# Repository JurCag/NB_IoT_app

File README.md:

# NB-IoT Application

Table of contents:
- [Introduction](#introduction)
- [System Architecture](#system-architecture)
- [Web Application](#web-application)
- [Firmware and Hardware](#firmware-and-hardware)
    - [Communication overview](#communication-overview)
    - [Development tools](#development-tools)
  - [NB-IoT Concentrator](#nb-iot-concentrator)
    - [Firmware](#firmware)
    - [Hardware](#hardware)
  - [Sensor Boards](#sensor-boards)
    - [Firmware](#firmware)
    - [Hardware](#hardware)
 
#### Introduction:
Project showcases the application of NB-IoT technology for uploading data to the cloud. 
Hardware involves an NB-IoT concentrator and 6 sensor nodes equipped with different sensors, specifically designed to measure parameters of a [photobioreactor](https://en.wikipedia.org/wiki/Photobioreactor).<br />
Simple concept of the application including PBR is available [here](https://github.com/JurCag/NB_IoT_app/blob/master/images/photobioreactor.svg).

#### System Architecture:
<div align="center">

</div>

## Web Application

#### Description:
Simple web application for sensor data visualization and control of NB-IoT concentrator.

#### External libraries:
- AWS SDK: to access AWS services
- JSZip: to manipulate ZIP files
- Highcharts: data visualization

## Firmware and Hardware

#### Communication overview:
The application uses [MQTT](https://mqtt.org/) protocol to communicate with broker within the AWS IoT Core. MQTT topics and structure of JSON payloads sent in the messages is shown below.
1) The concentrator provisions new nodes into the BLE mesh network. Nodes provide their descriptors.
2) The user requests the node measurement period by publishing a message to the topic: **BG96_demoThing/mmtPeriods/command**.
3) The concentrator responds with the current measurement period of that node to the topic: **BG96_demoThing/mmtPeriods/response**.
4) The user can change the node measurement period (e.g. 10 minutes).
5) The concentrator confirms the change by repeating the message.
6) The concentrator stores the measurement period value into the NVS (Non-Volatile Storage) memory.
7) When the counter reaches the specified period, the concentrator requests data from the sensor node over the BLE mesh.
8) The sensor node sends measured data.
9) The concentrator uploads the sensory data to AWS on the MQTT topic: **BG96_demoThing/sensors/\<nodeName\>**.
  
<div align="center">
  
</div>

#### Development tools:
- VSCode + [PlatformIO](https://platformio.org/)
- Framework: ESP-IDF (within platformio project, no need to install separately)

### NB-IoT Concentrator 
#### Firmware:
- The concentrator, acting as a master device, collects measurement data from sensor nodes and uploads it to the AWS IoT Core.
- The concentrator also establishes a local BLE mesh network and provisions other nodes into the network.
- BLE mesh models implemented by concentrator:
  - Configuration Server
  - Configuration Client
  - Sensor Client 

#### Hardware:
[Custom PCB board](https://github.com/JurCag/NB_IoT_app/tree/master/NB-IoT_PCB_rev_1_1) with ESP32-C3 controller and Quectel BG96 module.

| Component     | Link  |
| :-----------  |:---------------:|
| **MCU**                 | [ESP32-C3](https://www.espressif.com/en/products/socs/esp32-c3) |
| **NB-IoT module**       | [Quectel BG96](https://www.quectel.com/product/lpwa-bg96-cat-m1-nb1-egprs) |
| **NB-IoT module board** | [LTE IoT 2 Click](https://www.mikroe.com/lte-iot-2-click) |
| **NB-IoT concentrator** | [NB-IoT_PCB_rev_1_1](https://github.com/JurCag/NB_IoT_app/tree/master/NB-IoT_PCB_rev_1_1) |

### Sensor boards
#### Firmware:
- Each sensor node incorporates the same BLE mesh models.
- BLE mesh models implemented by sensor nodes:
  - Configuration Server
  - Sensor Server 
  - Sensor Setup Server 
- The drivers are specific to the corresponding sensor they are equipped with.

#### Hardware:
 - **Control board:<br />**
 Each sensor node has the same control board: [ESP32-C3-DevKitC-02](https://docs.espressif.com/projects/esp-idf/en/latest/esp32c3/hw-reference/esp32c3/user-guide-devkitc-02.html)

 - **Sensors:<br />**

| Physical quantities        |     Sensor        |  Connection     | 
| :-----------: |:---------------:|:---------------:|
| temperature,<br /> humidity,<br /> pressure | BME280    ||
| pH                                          | PH4502C   ||
| CO_2 concentration                          | MHZ19B    ||
| light intensity                             | GL5528    ||
| turbidity                                   | TS300B    ||
| electric current                            | ACS712    ||

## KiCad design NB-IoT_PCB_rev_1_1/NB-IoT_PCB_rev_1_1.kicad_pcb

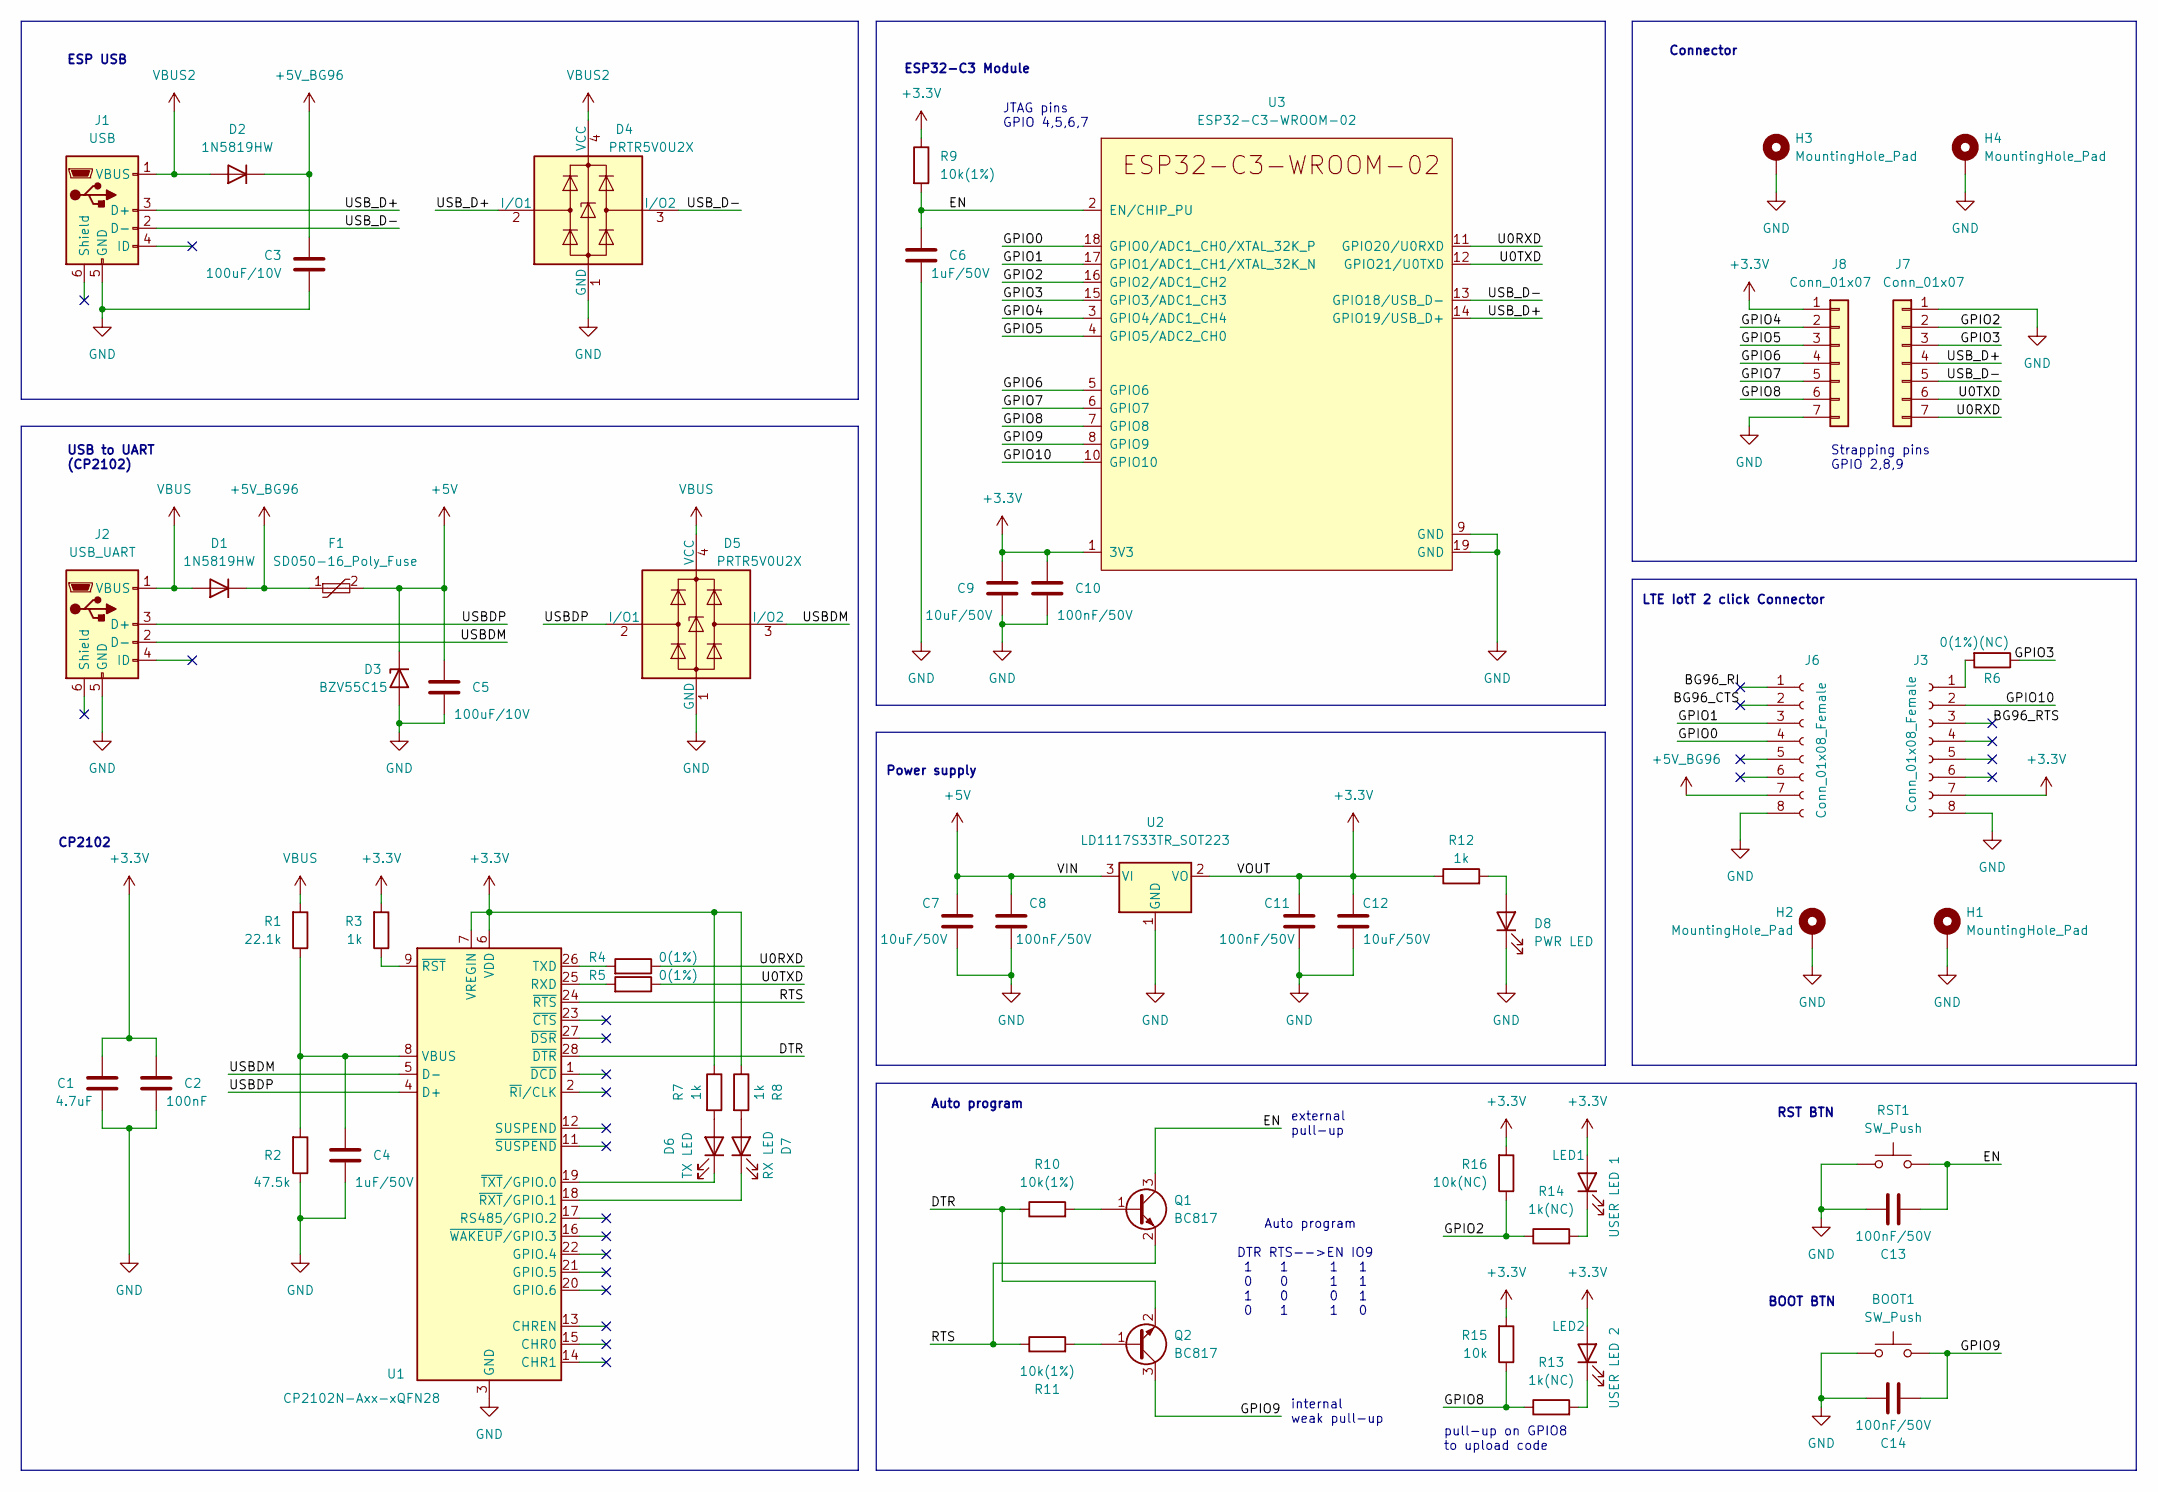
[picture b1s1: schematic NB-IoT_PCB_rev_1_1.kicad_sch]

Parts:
BOOT1: SW_Push; SW_PUSH_6mm_H5mm
C1: 4.7uF; C_1210_3225Metric_Pad1.33x2.70mm_HandSolder
C2: 100nF; C_0603_1608Metric_Pad1.08x0.95mm_HandSolder
C3, C5: 100uF/10V; CP_Radial_D5.0mm_P2.00mm
C4, C6: 1uF/50V; C_0603_1608Metric_Pad1.08x0.95mm_HandSolder
C7, C12: 10uF/50V; C_0805_2012Metric_Pad1.18x1.45mm_HandSolder
C8, C10, C11, C13, C14: 100nF/50V; C_0603_1608Metric_Pad1.08x0.95mm_HandSolder
C9: 10uF/50V; C_1206_3216Metric_Pad1.33x1.80mm_HandSolder
D1, D2: 1N5819HW; SOD3715X145N
D3: BZV55C15; D_MiniMELF
D4, D5: PRTR5V0U2X; SOT-143_Handsoldering
D6: TX LED; D_0805_2012Metric_Pad1.15x1.40mm_HandSolder
D7: RX LED; D_0805_2012Metric_Pad1.15x1.40mm_HandSolder
D8: PWR LED; D_0805_2012Metric_Pad1.15x1.40mm_HandSolder
F1: SD050-16_Poly_Fuse; FP_for_SD050-16_POLY_FUSE
H1, H2, H3, H4: MountingHole_Pad; MountingHole_3.2mm_M3_Pad_Via
J1: USB; USB_Micro-B_Amphenol_10118194_Horizontal
J2: USB_UART; USB_Micro-B_Amphenol_10118194_Horizontal
J3, J6: Conn_01x08_Female; PinSocket_1x08_P2.54mm_Vertical
J7, J8: Conn_01x07; PinSocket_1x07_P2.54mm_Vertical
LED1: USER LED 1; D_0805_2012Metric_Pad1.15x1.40mm_HandSolder
LED2: USER LED 2; D_0805_2012Metric_Pad1.15x1.40mm_HandSolder
Q1, Q2: BC817; SOT-23
R1: 22.1k; R_0603_1608Metric_Pad0.98x0.95mm_HandSolder
R2: 47.5k; R_0603_1608Metric_Pad0.98x0.95mm_HandSolder
R3, R7, R8, R12: 1k; R_0603_1608Metric_Pad0.98x0.95mm_HandSolder
R4, R5: 0(1%); R_0603_1608Metric_Pad0.98x0.95mm_HandSolder
R6: 0(1%)(NC); R_0603_1608Metric_Pad0.98x0.95mm_HandSolder
R9, R10, R11: 10k(1%); R_0603_1608Metric_Pad0.98x0.95mm_HandSolder
R13, R14: 1k(NC); R_0603_1608Metric_Pad0.98x0.95mm_HandSolder
R15: 10k; R_0603_1608Metric_Pad0.98x0.95mm_HandSolder
R16: 10k(NC); R_0603_1608Metric_Pad0.98x0.95mm_HandSolder
RST1: SW_Push; SW_PUSH_6mm_H5mm
U1: CP2102N-Axx-xQFN28; QFN-28-1EP_5x5mm_P0.5mm_EP3.35x3.35mm
U2: LD1117S33TR_SOT223; SOT-223-3_TabPin2
U3: ESP32-C3-WROOM-02

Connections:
+3.3V: C1.2, C2.2, C9.2, C10.1, C11.1, C12.1, J3.7, J8.1, LED1.2 (A), LED2.2 (A), R3.2, R7.1, R8.1, R9.1, R12.1, R15.2, R16.2, U1.6 (VDD), U1.7 (VREGIN), U2.2 (VO), U3.1 (3V3)
+5V: C5.1, C7.1, C8.1, D3.1 (K), F1.2, U2.3 (VI)
+5V_BG96: C3.1, D1.2 (K), D2.2 (K), F1.1, J6.7
/BG96_CTS: J6.2
/BG96_RI: J6.1
/BG96_RTS: J3.3
/DTR: Q2.2 (E), R10.1, U1.28 (~DTR)
/EN: C6.1, C13.2, Q1.3 (C), R9.2, RST1.2, U3.2 (EN/CHIP_PU)
/GPIO0: J6.4, U3.18 (GPIO0/ADC1_CH0/XTAL_32K_P)
/GPIO1: J6.3, U3.17 (GPIO1/ADC1_CH1/XTAL_32K_N)
/GPIO2: J7.2, R14.1, R16.1, U3.16 (GPIO2/ADC1_CH2)
/GPIO3: J7.3, R6.1, U3.15 (GPIO3/ADC1_CH3)
/GPIO4: J8.2, U3.3 (GPIO4/ADC1_CH4)
/GPIO5: J8.3, U3.4 (GPIO5/ADC2_CH0)
/GPIO6: J8.4, U3.5 (GPIO6)
/GPIO7: J8.5, U3.6 (GPIO7)
/GPIO8: J8.6, R13.1, R15.1, U3.7 (GPIO8)
/GPIO9: BOOT1.2, C14.2, Q2.3 (C), U3.8 (GPIO9)
/GPIO10: J3.2, U3.10 (GPIO10)
/RTS: Q1.2 (E), R11.1, U1.24 (~RTS)
/U0RXD: J7.7, R4.1, U3.11 (GPIO20/U0RXD)
/U0TXD: J7.6, R5.1, U3.12 (GPIO21/U0TXD)
/USBDM: D5.3 (I/O2), J2.2 (D-), U1.5 (D-)
/USBDP: D5.2 (I/O1), J2.3 (D+), U1.4 (D+)
/USB_D+: D4.2 (I/O1), J1.3 (D+), J7.4, U3.14 (GPIO19/USB_D+)
/USB_D-: D4.3 (I/O2), J1.2 (D-), J7.5, U3.13 (GPIO18/USB_D-)
GND: BOOT1.1, C1.1, C2.1, C3.2, C4.1, C5.2, C6.2, C7.2, C8.2, C9.1, C10.2, C11.2, C12.2, C13.1, C14.1, D3.2 (A), D4.1 (GND), D5.1 (GND), D8.1 (K), H1.1, H2.1, H3.1, H4.1, J1.5 (GND), J2.5 (GND), J3.8, J6.8, J7.1, J8.7, R2.1, RST1.1, U1.3 (GND), U1.29 (GND), U2.1 (GND), U3.9 (GND), U3.19 (GND)
unnamed: C4.2, R1.1, R2.2, U1.8 (VBUS)
unnamed: D6.1 (K), U1.19 (~TXT/GPIO.0)
unnamed: D6.2 (A), R7.2
unnamed: D7.1 (K), U1.18 (~RXT/GPIO.1)
unnamed: D7.2 (A), R8.2
unnamed: D8.2 (A), R12.2
unnamed: J3.1, R6.2
unnamed: LED1.1 (K), R14.2
unnamed: Q1.1 (B), R10.2
unnamed: Q2.1 (B), R11.2
unnamed: R3.1, U1.9 (~RST)
unnamed: R4.2, U1.26 (TXD)
unnamed: R5.2, U1.25 (RXD)
unnamed: LED2.1 (K), R13.2
VBUS: D1.1 (A), D5.4 (VCC), J2.1 (VBUS), R1.2
VBUS2: D2.1 (A), D4.4 (VCC), J1.1 (VBUS)

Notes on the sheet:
CP2102
Strapping pins GPIO 2,8,9
Power supply
Auto program DTR RTS-->EN IO9 1 1 1 1 0 0 1 1 1 0 0 1 0 1 1 0
internal weak pull-up
Auto program
Connector
LTE IotT 2 click Connector
JTAG pins GPIO 4,5,6,7
USB to UART (CP2102)
ESP USB
ESP32-C3 Module
pull-up on GPIO8 to upload code
external pull-up
RST BTN
BOOT BTN

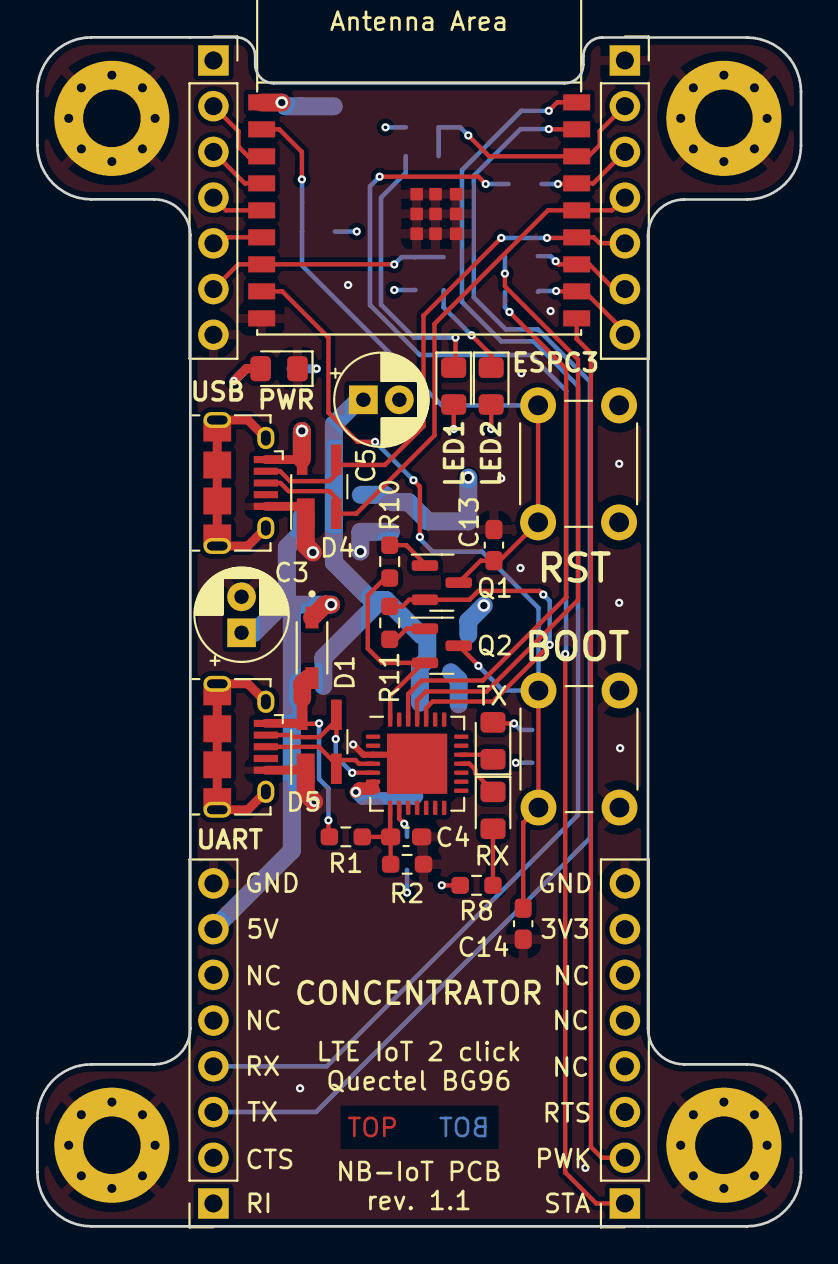
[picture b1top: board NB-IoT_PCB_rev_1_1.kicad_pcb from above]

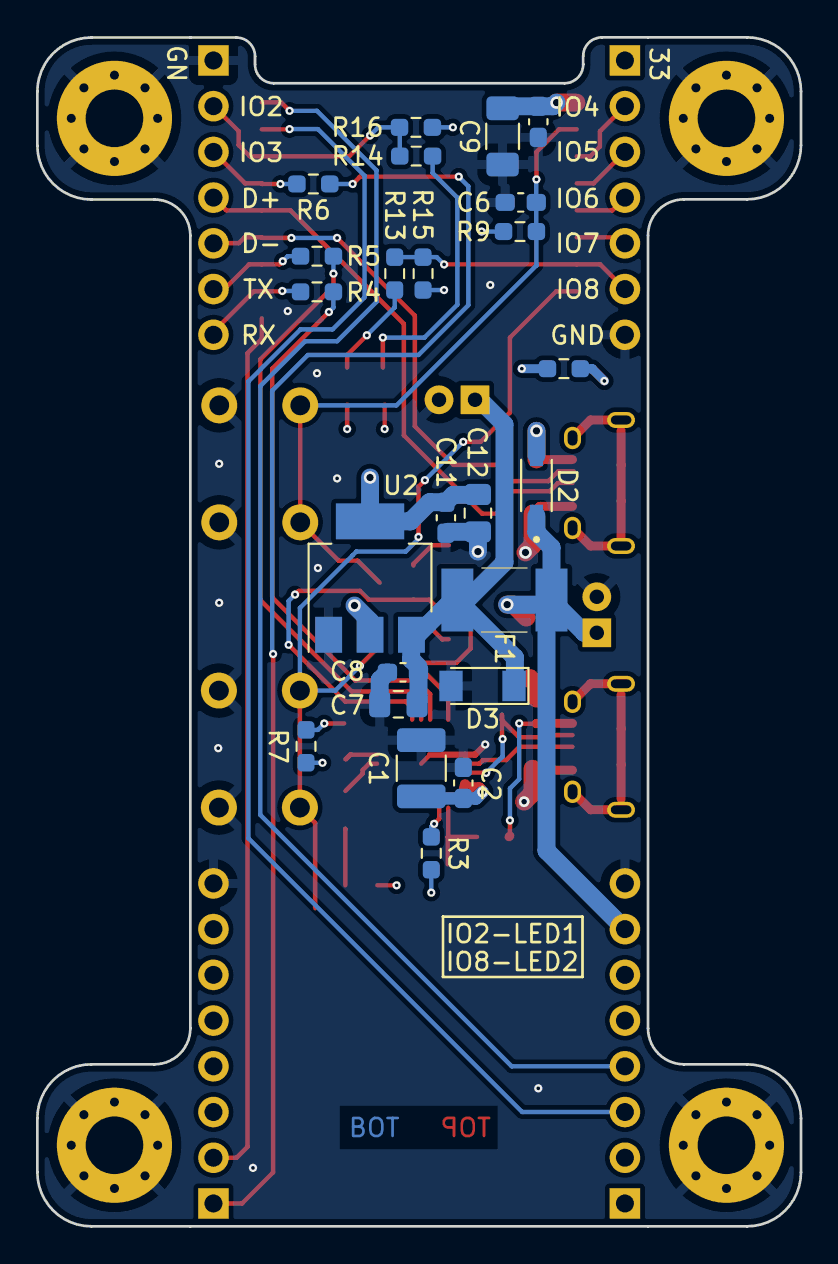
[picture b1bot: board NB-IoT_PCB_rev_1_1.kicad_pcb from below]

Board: 4 copper layers, 42.4 x 66.1 mm, 58 parts (24 on the bottom side), 40 nets.

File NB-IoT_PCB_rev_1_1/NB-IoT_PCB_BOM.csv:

Id;Designator;Package;Quantity;Designation;Supplier and ref
1;D3;D_MiniMELF;1;BZV55C15;https://www.tme.eu/cz/details/bzv55c15-cdi/zenerovy-diody-sm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
2;D4,D5;SOT-143_Handsoldering;2;PRTR5V0U2X;https://www.tme.eu/cz/sk/details/prtr5v0u2x.215/bezpecnostne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
3;J2;USB_Micro-B_Amphenol_10118194_Horizontal;1;USB_UART;https://cz.mouser.com/ProductDetail/Hirose-Connector/ZX62D-B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
4;C5,C3;CP_Radial_D5.0mm_P2.00mm;2;100uF/10V;
5;LED2;D_0805_2012Metric_Pad1.15x1.40mm_HandSolder;1;USER LED 2;
6;D8;D_0805_2012Metric_Pad1.15x1.40mm_HandSolder;1;PWR LED;
7;Q1,Q2;SOT-23;2;BC817;
8;R11,R10,R9;R_0603_1608Metric_Pad0.98x0.95mm_HandSolder;3;10k(1%);
9;J3,J6;PinSocket_1x08_P2.54mm_Vertical;2;Conn_01x08_Female;
10;D7;D_0805_2012Metric_Pad1.15x1.40mm_HandSolder;1;RX LED;
11;C13,C14,C2,C8,C10,C11;C_0603_1608Metric_Pad1.08x0.95mm_HandSolder;6;100nF/50V;
12;R12,R8,R3,R7;R_0603_1608Metric_Pad0.98x0.95mm_HandSolder;4;1k;
13;U1;QFN-28-1EP_5x5mm_P0.5mm_EP3.35x3.35mm;1;CP2102N-Axx-xQFN28;
14;LED1;D_0805_2012Metric_Pad1.15x1.40mm_HandSolder;1;USER LED 1;
15;J4,J5;PinSocket_1x05_P2.54mm_Vertical;2;Conn_01x05;
16;R1;R_0603_1608Metric_Pad0.98x0.95mm_HandSolder;1;22.1k;
17;D6;D_0805_2012Metric_Pad1.15x1.40mm_HandSolder;1;TX LED;
18;D1,D2;SOD3715X145N;2;1N5819HW;https://www.tme.eu/cz/sk/details/1n5819hw-7-f/diody-schottky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
19;RST1,BOOT1;SW_PUSH_6mm_H5mm;2;SW_Push;
20;U3;ESP32-C3-WROOM-02;1;ESP32-C3-WROOM-02;
21;C4;C_0603_1608Metric_Pad1.08x0.95mm_HandSolder;1;1uF/50V;
22;J1;USB_Micro-B_Amphenol_10118194_Horizontal;1;USB;https://cz.mouser.com/ProductDetail/Hirose-Connector/ZX62D-B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
23;R2;R_0603_1608Metric_Pad0.98x0.95mm_HandSolder;1;47.5k;
24;U2;SOT-223-3_TabPin2;1;LD1117S33TR_SOT223;https://www.tme.eu/cz/details/ld1117s33ctr/stabilizatory-nap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
25;F1;FP_for_SD050-16_POLY_FUSE;1;SD050-16_Poly_Fuse;http://www.tme.eu/cz/details/sd050-16/polymerove-pojistky-smd/ece/
26;R5,R4;R_0603_1608Metric_Pad0.98x0.95mm_HandSolder;2;0(1%);
27;R13,R14;R_0603_1608Metric_Pad0.98x0.95mm_HandSolder;2;1k(NC);
28;C9;C_1206_3216Metric_Pad1.33x1.80mm_HandSolder;1;10uF/50V;
29;R6;R_0603_1608Metric_Pad0.98x0.95mm_HandSolder;1;0(1%)(NC);
30;C6;C_1206_3216Metric_Pad1.33x1.80mm_HandSolder;1;1uF/50V;
31;C1;C_1210_3225Metric_Pad1.33x2.70mm_HandSolder;1;4.7uF;
32;C12,C7;C_0805_2012Metric_Pad1.18x1.45mm_HandSolder;2;10uF/50V;

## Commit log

2022-12-03 [1] Replace prepareArg() with more general prepAtCmdArgs() that takes array of void pointers with arguments. [2] Fix issue with commands being sent on 2nd try by introducing lastSentAtCmdStr variable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
2022-12-11 Add env:c3_debug to debug ESP through built-in JTAG interface. (also change PC uart pins)
2022-12-13 Create new sensor board project for BME280 (temperature, humidity, pressure)
2022-12-18 [1] Implement BLE mesh Sensor Server from ESP-IDF sensor_server example, and modify it so it sends measured data from the sensor using callback. [2] Implement reading of measurement data from BME280 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
2022-12-18 Remove unused files and some comments.
2022-12-20 Remove some comments and add nbiot_ble_mesh_common.
2023-01-03 [1] Implement BLE mesh provisioner & sensor client from ESP-IDF sensor_client example with modifications to forward gathered sensor data. [2] Implement interface which connects BLE mesh and BG96 part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
2023-01-04 [1] Add timeoutCnt to NbiotBleMeshNode_t and functions to keep track of how many times each node times out. [2] Edit tracking of node being provisioned to be tracked from the moment provisioner recei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
2023-01-04 Create new project for concentrator board pcb rev 1.0 based on breadboard_demo. Yet no modifications.
2023-01-06 Modify descriptor to custom nbiotSensorServerDescriptor_t which adds to original descriptor new data specified in struct NbiotSensorSetup_t. Implement it on both, provisioner and sensor server sides.
2023-01-08 Remove #include nbiot_ble_mesh_node_bme280.h. Must be independent from layers that build on top of it.
2023-01-08 Pack BLE mesh server functionality into 'server_include' and 'server_src' folders. Specific sensor server nodes should be build on top of it.
2023-01-08 [1] Extend the NbiotSensorSetup_t by measurement unit. [2] Provisioner now waits to start gathering sensor data after the GSM connection is established. (Still leave an option to gather data even if 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
2023-01-08 Create new sensor board project for photoresistor (light intensity).
2023-01-11 FW for NB-IoT PCB rev 1.0. Both GSM and BLE Mesh components tested. FW is just modified breadboard demo but no significant changes.
2023-01-13 [1] Change structure of json data being send to AWS. Whole data of one node is within one mqtt packet.[2] Fix uartRx task to build incoming data even if longer than UART THRESHOLD.
2023-01-15 Edit BG96_mqtt to restart esp if the connection to mqtt server fails.
2023-01-15 Create new sensor board project for ACS712 (dc current sensor).
2023-01-23 Create new sensor board project for MHZ19B (CO2 concentration sensor).
2023-01-25 [1] Edit nbiot_ble_mesh_bg96_interface to send mqtt data from separate task. Now its possible to send payload data of more than 1024 bytes. [2] Add testing of NB IoT upload datarate.
2023-01-28 ESP <--> BG96 AT communication redesign. taskAtPacketTxScheduler manages AT packets to be sent to taskTx while packets are still being queued by queueAtPacket function, which can be called from anywh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
2023-01-28 Redesign the BG96_atCmdFamilyParser and BG96_mqttResponseParser to be able to resend the same payload in case when AT cmd was successfully sent to BG96, but the mqtt publish failed.
2023-01-29 Create new sensor board project for TS-300B (turbidity).
2023-01-30 Replace net_buf_simple_push, which caused ESP to restart for unknown reason, with net_buf_simple_add_le16. And correct the buffer size.
2023-01-31 Create new sensor board project for 4502C (pH of liquids).
2023-01-31 Update NbiotBLEMeshProperties_t across all projects (formality, no functional impact).
2023-01-31 Update size of NET_BUF_SIMPLE_DEFINE_STATIC across sensor projects.
2023-02-12 Create simple sensor measurements dashboard for Amazon S3 buckets.
2023-02-12 Edit BG96_sendMqttData to take also mqtt topic as input. Important change in taskAtPacketTxScheduler to multiply the response time by max number of resend attempts.
2023-02-25 Subscribe to BG96_demoThing/mmtPeriods/command topic and functionality to change mmt periods of individual nodes.
2023-02-25 Update web page to publish msgs which change nodes mmt period.
2023-03-05 New dashboard web app with option to download mmt data in .csv files
2023-03-08 Add functionality to ask concentrator for nodes mmt period whenever switched to live mode.
2023-03-11 Calibrate conversion from mV to current.
2023-03-12 [1] Add functionality to query individual nodes mmt period (for the web app). [2] Option to name nodes according to their sensor. [3] Functionality to RE-OPEN MQTT connection.
2023-03-12 Change pressure units to kPa
2023-03-14 Change turbidity units and calculation from NTU to dimensionless, since NTU calibration is very hard to achieve.
2023-03-14 [1] Callibration of pH sensor offset (on pH = 7), but gain not compensated yet. [2] Remove concentrator_pcb_rev_1_1 project, which was added accidentally.
2023-04-01 Add overhead testing and initial wait procedure when connecting into NB-IoT network.
2023-04-10 Fix timezone issue
2023-04-10 Added functionality to store nodes measurement periods in NVS partition of flash memory
2023-05-16 Calibration and minor changes of sensor board projects.
2023-05-16 Minor changes, LED indication and some comments before submission.
2023-05-18 Add images.
2023-05-18 Add KiCad concentrator project.
2023-05-18 Add more images.
2023-05-18 White bg.
